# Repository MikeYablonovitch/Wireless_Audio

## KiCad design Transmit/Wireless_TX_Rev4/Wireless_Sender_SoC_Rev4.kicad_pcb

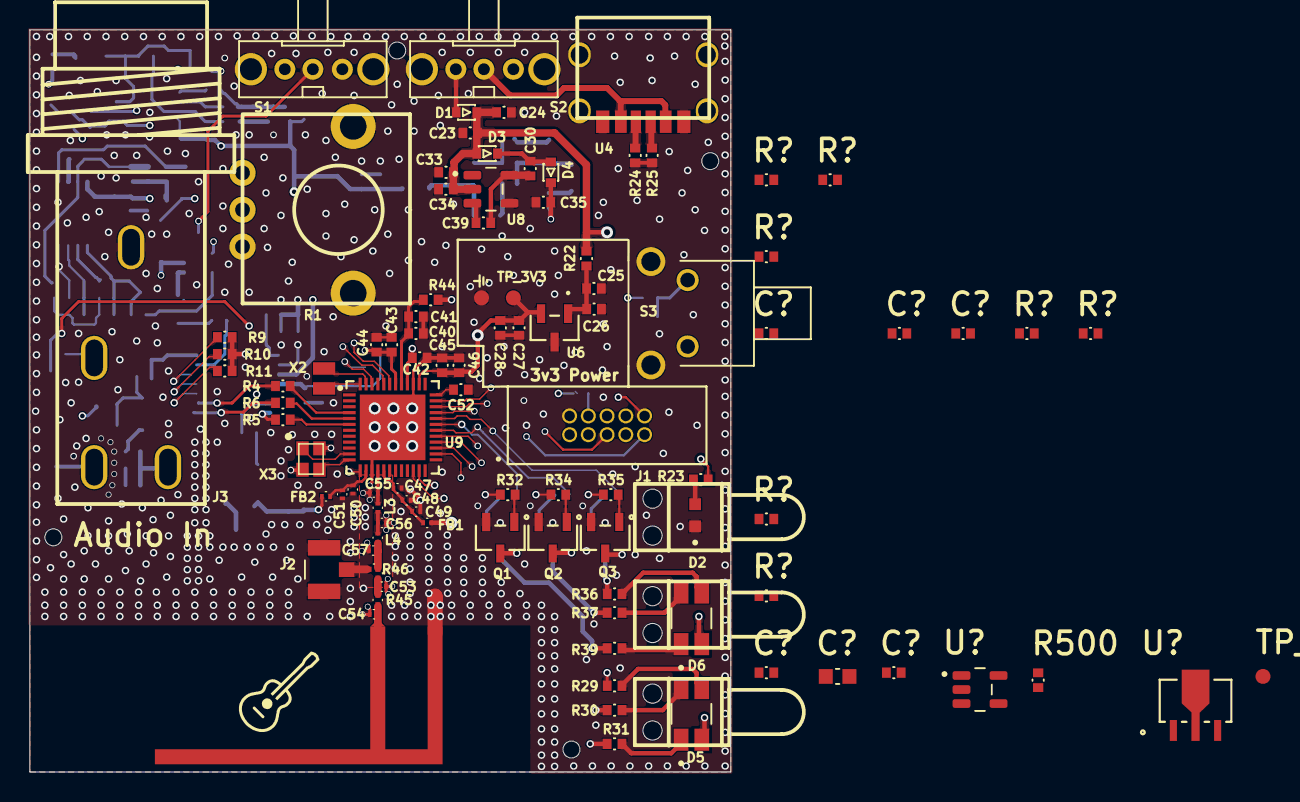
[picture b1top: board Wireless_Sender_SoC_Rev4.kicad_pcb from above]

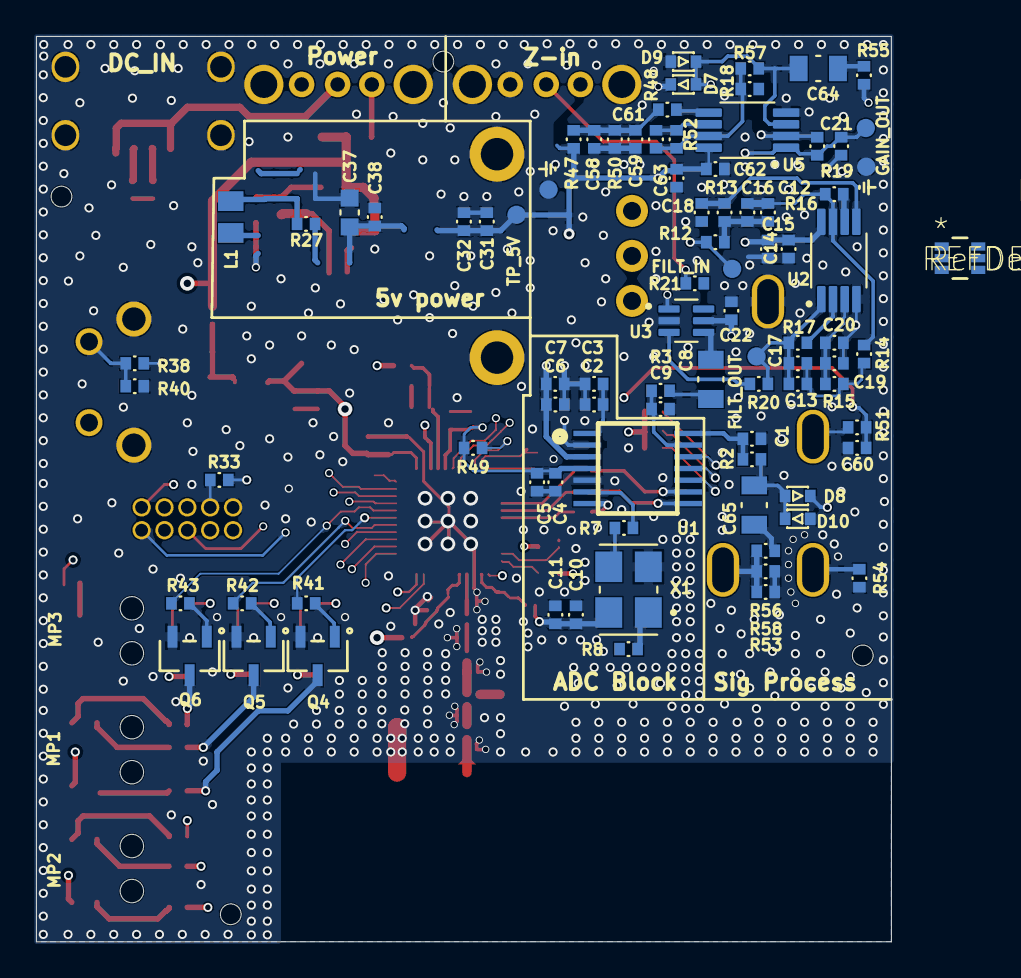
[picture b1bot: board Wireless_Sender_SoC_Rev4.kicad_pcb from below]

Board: 4 copper layers, 47.5 x 50.3 mm, 187 parts (87 on the bottom side), 112 nets.

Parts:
AT1: INVERTED_F
C1: DNP; Capacitor_0402
C2, C5, C6, C10, C24, C26, C41, C42, C44, C45: 100n; CAPACITOR_0402
C3, C4, C7, C11: 2u2; CAPACITOR_0402
C8, C64, C65: 100n; CAPACITOR_0805
C9, C21, C61: DNP; CAPACITOR_0402
C12, C13, C18: 2n7; CAPACITOR_0402
C14, C27, C31, C38, C40, C43, C52, C59, C62: 1u; CAPACITOR_0402
C15, C28, C32, C46, C63: 10u; CAPACITOR_0402
C16, C19: 390p; CAPACITOR_0402
C17: 4n7; CAPACITOR_0402
C20: 680p; CAPACITOR_0402
C22, C23: 1u; Capacitor_0402
C25, C30, C33, C35, C39: 2u2; Capacitor_0402
C34: 100n; Capacitor_0402
C37: 10u; CAPACITOR_0603
C47: 0p5; CAPACITOR_0201
C48, C50: 18p; CAPACITOR_0201
C49: 1u; CAPACITOR_0201
C51: 2u2; CAPACITOR_0201
C53, C54: DNP; CAPACITOR_0201
C55: 2p3; CAPACITOR_0201
C56: 1p6; CAPACITOR_0201
C57: 0p3; CAPACITOR_0201
C58: 10n; CAPACITOR_0402
C60: 1nF; CAPACITOR_0402
C?: 1u; Capacitor_0402
C?#2: 10n; Capacitor_0402
C?#3: 10u; Capacitor_0402
C?#4: 10u; Capacitor_0603
C?#5, C?#6: 1u; Capacitor_0402
D1, D3, D4: 300mV; SOD523
D2: 0603 LED; LED_SM0603UYC
D5, D6: LED RGB DIFFUSED CHIP SMD; LED_HSMF-C118
D7, D8, D9, D10: 370mV; SOD523
FB1, FB2: BLM03AG700SN1D; FERRITE_BEAD_0201
J1: CONN HEADER VERT 10POS 1.27MM; CONN_3220-10-0100-00_CNC
J2: U.FL-R-SMT; HIROSE_U.FL-R-SMT-1(80)
J3: -20℃~+70℃ 6.35mm Headphone Jack 30V 500mA Plugin 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; AUDIO-TH_PJ-603
L1: 3.3uH; INDUCTOR 0805
L3: 2n9; INDUCTOR_0201
L4: 1n2; INDUCTOR_0201
MP1, MP2, MP3: SLP3-200-200-R
Q1, Q2, Q3, Q4, Q5, Q6: MOSFET N-CH 60V 115MA SOT23; SOT-23_MCC
R1: 10K_Pot; RK09L1140
R2, R3, R18, R32, R34, R35, R38, R41, R42, R43, R52, R55, R56: 1k; RESISTOR_0402
R4, R5, R6, R7, R19, R20, R33: 49r9; RESISTOR_0402
R8, R9, R10, R11, R23, R40, R47, R48, R50: 10k; RESISTOR_0402
R12, R13, R14, R15, R16, R17, R29, R30, R31, R36, R37, R39: 5.6k; RESISTOR_0402
R21, R24, R25: 10k; Resistor_0402
R22: 0r; RESISTOR_0402
R27, R44: 2r; RESISTOR_0402
R45: 0r; RESISTOR_0201
R46: 0r; RESISTOR_0201 - 2-WAY
R49, R53, R54: 10M; RESISTOR_0402
R51: 100k; RESISTOR_0402
R57: 1M; RESISTOR_0402
R58: 24k9; RESISTOR_0402
R500: DNP; Resistor_0402
R?: DNP; Resistor_0402
R?#2, R?#4, R?#6, R?#7: DNP; Resistor_0402
R?#3, R?#5: 1k; Resistor_0402
S1, S2: Slide Switch; OS102011MA1Q
S3: Switch Push Button; SW_1-1825027-1
TP_3V3, TP_5V: Test Point; TEST_POINT_ROUND_40
TP_CP: Test Point; TEST_POINT_ROUND_40
TP_FILT_IN: Test Point; TEST_POINT_ROUND_40
TP_FILT_OUT: Test Point; TEST_POINT_ROUND_40
TP_GAIN_OUT: Test Point; TEST_POINT_ROUND_40
TP_GND1, TP_GND2, TP_GND3: Test Point; TEST_POINT_ROUND_40_GND
U1: 24 serial TSSOP-14 ADCs/DACs - Special Purpose RO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; TSSOP-14
U2, U5: OPA2376AIDGKR; SOP65P490X110-8N
U3: IC SWITCH SPDT X 1 15OHM SC70-6; SOT65P210X110-6N
U4: TYPE-C 6P(073)
U6: IC REG LIN 3.3V 300MA SOT23-3; AP7375-33SA-7_DIO
U8: UNREGULATED 60-mA CHARGE PUMP VOLTAGE INVERTER; SOT95P280X145-5N
U9: EFR32MG24B220F1536IM48-B; QFN48_0p4_6sq_SIL
U?: IC REG LINEAR 5.5V 150MA SOT-89-3; SOT-89_3MC_MCH
U?#2: TPS7A2050 - 5V 300MA SOT23-5; SOT95P280X145-5N
U?#3: MCP4017T-103E/LTY; SOP_MCP4017T-103ELTY_MCH
X1: 12.288MHz 3.3V ±10ppm CMOS; XTAL_ASFL1-12.288MHZ-EC-T
X2: 32.768kHz; DST210AC
X3: 39MHz 10pF ±8ppm; TZ3541C

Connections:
3V_DIGITAL: C4.1, C5.1, C10.1, C11.1, C27.1, C28.1, C42.1, C43.1, C44.1, C45.1, C46.1, FB1.2, FB2.2, J1.1, R1.1, R8.2, R9.2, R10.2, R11.2, R44.2, R49.2, S3.1, TP_3V3.1, U1.4, U6.2, U9.38, U9.40, U9.42, X1.4
5V_ANALOG: C6.1, C7.1, C14.1, C15.1, C22.1, C31.1, C32.1, C62.1, C63.1, C?.1, C?#3.1, D7.Cathode, D8.Cathode, R21.1, R47.2, TP_5V.1, U1.3, U2.8, U3.5, U5.8, U?#2.5, U?#3.1
ADC_I2S_BCLK: R6.1, U9.5
ADC_I2S_DATA: R4.1, U9.4
ADC_I2S_LRCLK: R5.2, U9.6
ANTI_ALIAS_IN: R12.2, R19.1, R?#4.1, TP_FILT_IN.1
ANTI_ALIAS_OUT: C13.2, C17.2, R17.1, R20.1, TP_FILT_OUT.1, U2.1
ANT_OUT: C53.1, R45.1, R46.2
ANT_OUT_MATCHED: AT1.1, C54.1, R45.2
AUDIO_HOT_PLUG_DETECT: C60.2, R49.1, R51.1, U9.46
BUTTON_IN: R38.1, U9.35
FMT: R9.1, U1.12
GAIN_OUT: C21.1, R19.2, R?#5.2, TP_GAIN_OUT.1, U5.1
GND: AT1.2, C1.2, C2.2, C3.2, C4.2, C5.2, C6.2, C7.2, C9.2, C10.2, C11.2, C14.2, C15.2, C18.2, C19.2, C20.2, C22.2, C23.1, C24.1, C25.2, C26.2, C27.2, C28.2, C31.2, C32.2, C33.2, C34.2, C35.2, C37.2, C38.2, C40.2, C41.2, C42.2, C43.2, C44.2, C45.2, C46.2, C47.2, C48.2, C49.2, C50.2, C51.2, C52.2, C53.2, C54.2, C55.2, C56.2, C57.2, C58.2, C59.2, C60.1, C62.2, C63.2, C?#2.2, C?#4.2, C?#5.2, C?#6.2, D2.C, D9.Anode, D10.Anode, J1.2, J2.G1, J2.G2, J3.2, Q1.2, Q2.2, Q3.2, Q4.2, Q5.2, Q6.2, R1.3, R1.4, R1.5, R24.2, R25.2, R40.2, R50.2, R53.1, R54.1, R58.1, R500.2, R?.1, R?#2.2, R?#4.2, R?#6.2, R?#7.1, S1.1, S1.MT1, S1.MT2, S2.MT1, S2.MT2, S3.S1, S3.S2, TP_GND1.1, TP_GND2.1, TP_GND3.1, U1.2, U1.5, U2.4, U3.2, U4.A12, U4.B12, U4.SHIELD, U5.4, U6.3, U8.4, U9.15, U9.39, U9.49, U?#2.2, X1.2, X3.2, X3.4
HFXTAL_I: U9.11, X3.1
HFXTAL_O: U9.12, X3.3
LFXO_I: U9.47, X2.1
LFXO_O: U9.48, X2.2
MD0: R11.1, U1.10
MD1: R10.1, U1.11
NetC1_1: C1.1, R2.1, U1.14
NetC2_1: C2.1, C3.1, U1.1
NetC8_1: C8.1, R3.2
NetC9_1: C9.1, R3.1, U1.13
NetC12_1: C12.1, C16.1, R12.1, R13.2
NetC12_2: C12.2, C16.2, R14.2, R16.1, U2.7
NetC13_1: C13.1, C17.1, R14.1, R15.2
NetC18_1: C18.1, R13.1, U2.5
NetC19_1: C19.1, C20.1, R15.1, U2.3
NetC21_2: C21.2, R?#3.2, U5.2
NetC25_1: C25.1, C26.1, R22.1, U6.1
NetC30_1: C30.1, D3.Cathode, D4.Anode
NetC30_2: C30.2, C39.1, U8.5
NetC35_1: C35.1, D4.Cathode, L1.2, TP_CP.1
NetC37_1: C37.1, C38.1, C?#6.1, U?.3, U?#2.1, U?#2.3
NetC39_2: C39.2, U8.3
NetC40_1: C40.1, C41.1, R44.1, U9.41
NetC47_1: C47.1, C48.1, C49.1, FB1.1, U9.17
NetC50_1: C50.1, C51.1, FB2.1, U9.14
NetC52_1: C52.1, U9.36
NetC56_1: C56.1, L3.2, L4.1
NetC58_1: C58.1, C59.1, R47.1, R48.1, R50.1
NetC61_2: C61.2, R52.2, U5.6
NetC64_2: C64.2, R55.1
NetC65_2: C65.2, R56.1
NetC?_1: C?#4.1, C?#5.1, R27.1, U?.2
NetC?_2: C?.2, C?#3.2, U?#3.2
NetD1_Anode: D1.Anode, S2.3
NetD2_A: D2.A, R23.2
NetD5_2: D5.2, R29.2
NetD5_3: D5.3, R30.2
NetD5_4: D5.4, R31.2
NetD6_2: D6.2, R36.2
NetD6_3: D6.3, R37.2
NetD6_4: D6.4, R39.2
NetJ1_4: J1.4, R33.2
NetJ3_3: J3.3, R51.2
NetL1_1: L1.1, R27.2
NetQ1_1: Q1.1, R32.1
NetQ1_3: Q1.3, R31.1
NetQ2_1: Q2.1, R34.2
NetQ2_3: Q2.3, R30.1
NetQ3_1: Q3.1, R35.1
NetQ3_3: Q3.3, R29.1
NetQ4_1: Q4.1, R41.1
NetQ4_3: Q4.3, R39.1
NetQ5_1: Q5.1, R42.2
NetQ5_3: Q5.3, R37.1
NetQ6_1: Q6.1, R43.2
NetQ6_3: Q6.3, R36.1
NetR4_2: R4.2, U1.9
NetR5_1: R5.1, U1.7
NetR6_2: R6.2, U1.8
NetR7_2: R7.2, X1.3
NetR8_1: R8.1, X1.1
NetR16_2: R16.2, U2.6
NetR17_2: R17.2, U2.2
NetR18_2: R18.2, R?#3.1, U?#3.5
NetR20_2: R20.2, R?#2.1, U3.3
NetR21_2: R21.2, S1.2, U3.6
NetR24_1: R24.1, U4.B5
NetR25_1: R25.1, U4.A5
NetR38_2: R38.2, R40.1, S3.2
NetR48_2: R48.2, U5.5
NetR?_1: R?#5.1, U?#3.6
NetS2_2: S2.2, U4.A9, U4.B9
OP_AMP_BIAS: C61.1, R18.1, R52.1, R57.1, R?#6.1, U5.7
PTI_DATA: J1.10, U9.44
PTI_FRAME: J1.9, U9.43
Pot_Output: C?#2.1, R1.2
RESET: J1.3, U9.13
RF_OUT: C55.1, L3.1, U9.16
RF_OUT_MATCHED: C57.1, L4.2, R46.1
RGB_1_B_PWM: R32.2, U9.22
RGB_1_G_PWM: R34.1, U9.23
RGB_1_R_PWM: R35.2, U9.26
RGB_2_B_PWM: R41.2, U9.31
RGB_2_G_PWM: R42.1, U9.30
RGB_2_R_PWM: R43.1, U9.32
SCK_FROM_TCXO: R7.1, U1.6
SLEEVE_BIAS_OUT: C65.1, D8.Anode, D10.Cathode, R2.2, R?#7.2
SLEEVE_SIGNAL_IN: J3.5, R53.2, R56.2, R58.2
SWCLK: J1.8, U9.27
SWDIO: J1.7, U9.28
SWO: J1.6, U9.29
TIP_ADC_IN: C8.2, R?.2, U3.4
TIP_SIGNAL_IN: J3.4, R54.2, R55.2
TIP_SIGNAL_IN_BIASED: C64.1, D7.Anode, D9.Cathode, R57.2, U3.1, U5.3
UFL_OUT: J2.SIG, R46.3
VCOM_RX: R33.1, U9.34
VCOM_TX: J1.5, U9.33
VIN: C23.2, C24.2, C33.1, C34.1, D1.Cathode, D3.Anode, D5.1, D6.1, R22.2, R23.1, U8.2

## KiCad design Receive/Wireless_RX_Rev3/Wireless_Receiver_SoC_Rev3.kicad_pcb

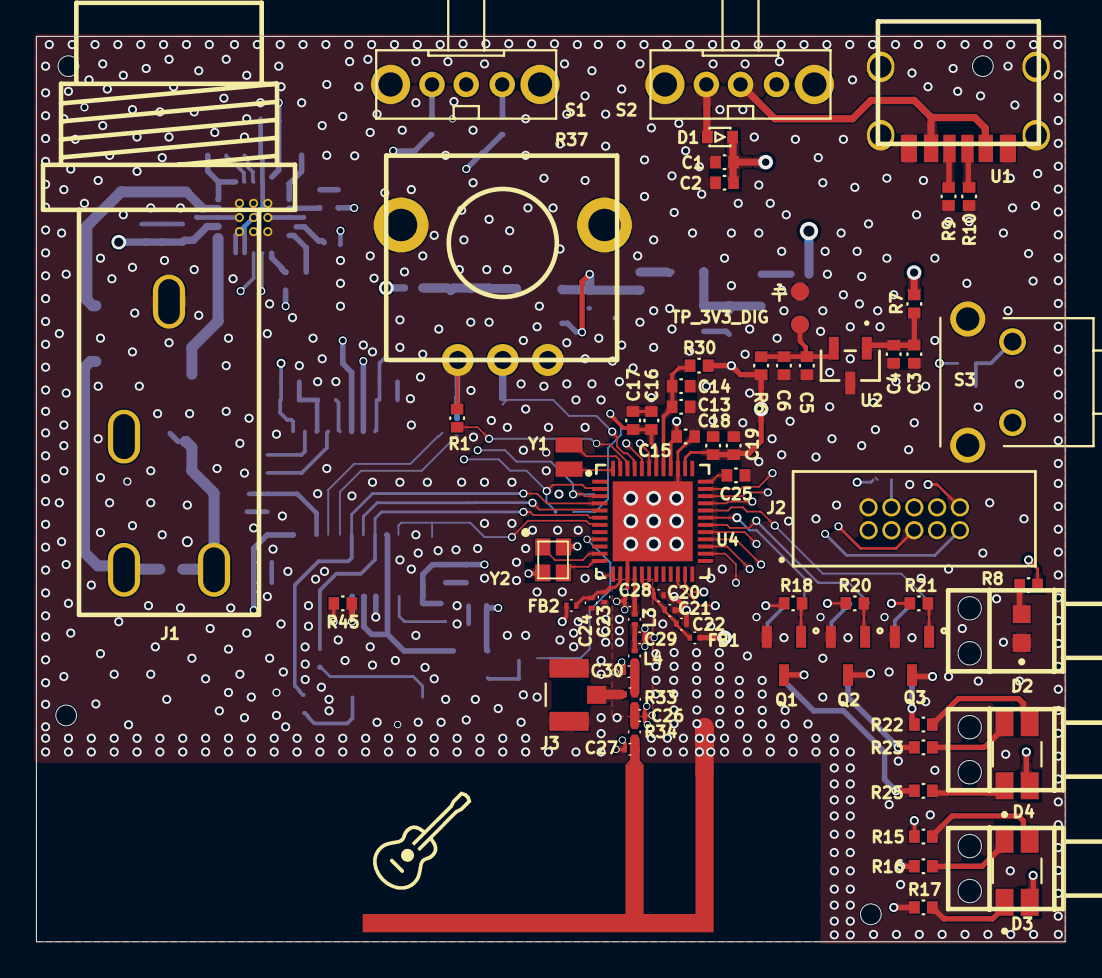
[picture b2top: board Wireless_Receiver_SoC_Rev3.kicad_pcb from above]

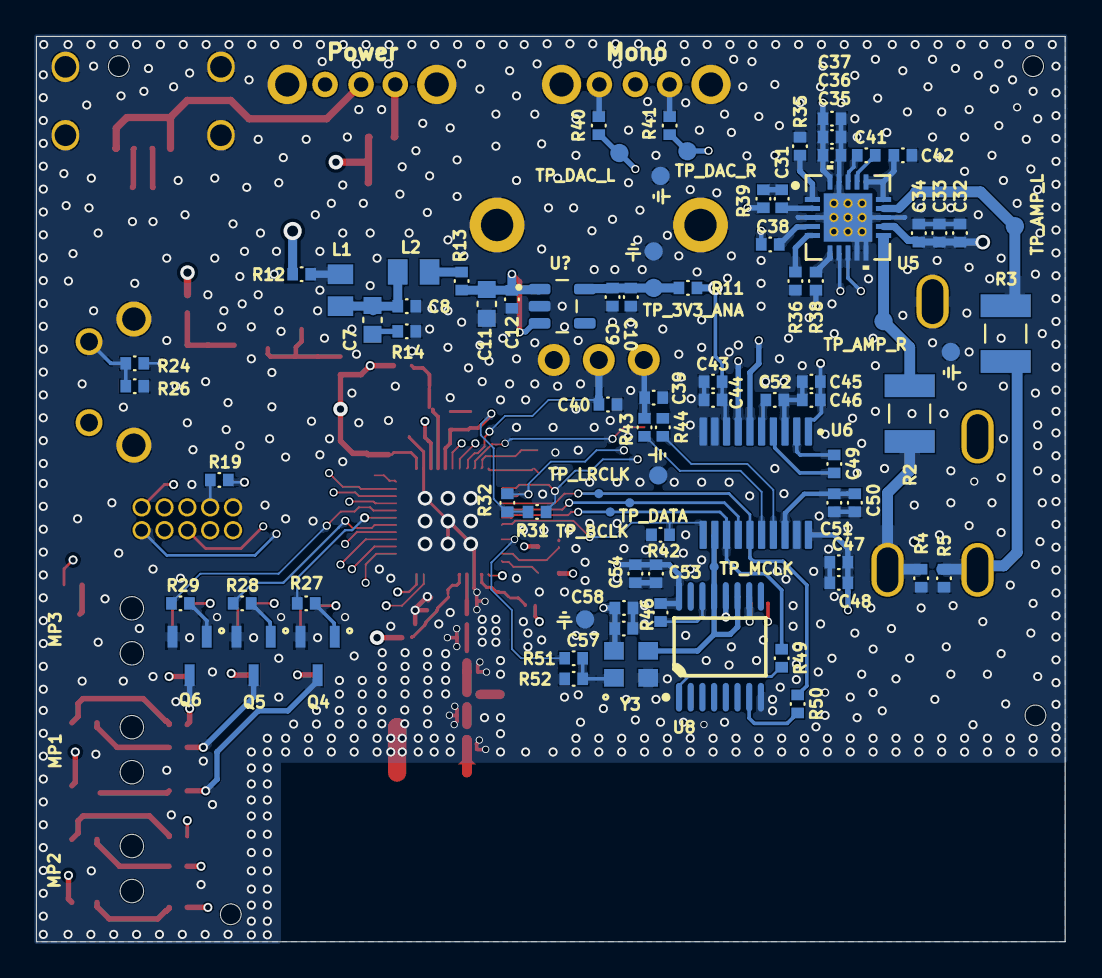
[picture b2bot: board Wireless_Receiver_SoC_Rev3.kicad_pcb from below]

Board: 4 copper layers, 57.1 x 50.3 mm, 158 parts (86 on the bottom side), 105 nets.

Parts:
AT1: INVERTED_F
C1, C9, C33, C36, C39, C41, C42, C44, C45, C48, C51, C54, C58: 1u; Capacitor_0402
C2, C34, C35, C46, C47, C53, C57: 100n; Capacitor_0402
C3: 2u2; Capacitor_0402
C4, C5, C8, C12, C13, C16, C25: 1u; CAPACITOR_0402
C6, C19: 10u; CAPACITOR_0402
C7, C11: 10u; CAPACITOR_0603
C10, C32, C37, C43, C50: 10u; Capacitor_0402
C14, C15, C17, C18: 100n; CAPACITOR_0402
C20: 0.5p; CAPACITOR_0201
C21, C23: 18p; CAPACITOR_0201
C22: 1u; CAPACITOR_0201
C24: 2.2u; CAPACITOR_0201
C26, C27: DNP; CAPACITOR_0201
C28: 2.3p; CAPACITOR_0201
C29: 1.6p; CAPACITOR_0201
C30: 0.3p; CAPACITOR_0201
C31, C38: 470n; Capacitor_0402
C40: 10n; Capacitor_0402
C49, C52: 2.2uF; Capacitor_0402
D1: 300mV; SOD523
D2: 0603 LED; LED_SM0603UYC
D3, D4: 1210 Red, Green, Blue (RGB); LED_HSMF-C118
FB1, FB2: BLM03AG700SN1D; FERRITE_BEAD_0201
J1: -20℃~+70℃ 6.35mm Headphone Jack 30V 500mA Plugin 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; AUDIO-TH_PJ-603
J2: CONN HEADER VERT 10POS 1.27MM; CONN_3220-10-0100-00_CNC
J3: U.FL-R-SMT; HIROSE_U.FL-R-SMT-1(80)
L1, L2: 3.3uH; INDUCTOR 0805
L3: 2.9n; INDUCTOR_0201
L4: 1.2n; INDUCTOR_0201
MP1, MP2, MP3: SLP3-200-200-R
Q1, Q2, Q3, Q4, Q5, Q6: MOSFET N-CH 60V 115MA SOT23; SOT-23_MCC
R1, R4, R5, R26: 10k; RESISTOR_0402
R2, R3: 39r; Resistor_1210
R6, R11, R35, R36: 0r; Resistor_0402
R7, R12: 0r; RESISTOR_0402
R8, R38, R42, R43, R44, R45, R46: 10k; Resistor_0402
R9, R10: 5k1; Resistor_0402
R13, R14, R30: 2r; RESISTOR_0402
R15, R16, R17, R22, R23, R25: 5.6k; RESISTOR_0402
R18, R20, R21, R24, R27, R28, R29: 1k; RESISTOR_0402
R19: 49r9; RESISTOR_0402
R31, R32: DNP; Resistor_0402
R33: Resistor_2-way-no-stub; RESISTOR_0201 - 2-WAY
R34: 0r; RESISTOR_0201
R37: 10K_Pot; RK09L1140
R39, R40, R41, R51: 1k; Resistor_0402
R49, R50: 49r9; Resistor_0402
R52: NC; Resistor_0402
S1, S2: Slide Switch; OS102011MA1Q
S3: Switch Push Button; SW_1-1825027-1
TP_3V3_ANA, TP_3V3_DIG: Test Point; TEST_POINT_ROUND_40
TP_AMP_L: Test Point; TEST_POINT_ROUND_40
TP_AMP_R: Test Point; TEST_POINT_ROUND_40
TP_BCLK: Test Point; TEST_POINT_ROUND_20
TP_DAC_L: Test Point; TEST_POINT_ROUND_40
TP_DAC_R: Test Point; TEST_POINT_ROUND_40
TP_DATA: Test Point; TEST_POINT_ROUND_20
TP_GND1, TP_GND2: Test Point; TEST_POINT_ROUND_40_GND
TP_GND?: Test Point; TEST_POINT_ROUND_40_GND
TP_GND?#2, TP_GND?#3, TP_GND?#4: Test Point; TEST_POINT_ROUND_40_GND
TP_LRCLK: Test Point; TEST_POINT_ROUND_20
TP_MCLK: Test Point; TEST_POINT_ROUND_20
U1: TYPE-C 6P(073)
U2: IC REG LIN 3.3V 300MA SOT23-3; AP7375-33SA-7_DIO
U4: EFR32MG24B220F1536IM48-B; QFN48_0P4_6SQ_SIL
U5: Class AB QFN-20-EP(4x4) Audio Amplifiers; RTJ20_2P7X2P7
U6: PCM5100PWR; SOP65P640X120-20N
U8: IC BINARY COUNTER 8-BIT 16TSSOP; TI TSSOP-16 PW
U?: TPS7A2033PDBVR; SOT95P280X145-5N
Y1: SMD2012-2P Crystals ROHS; DST210AC
Y2: 39MHz 10pF ±8ppm SMD2016-4P Crystals ROHS; TZ3541C
Y3: 12.288MHz VCXO; SMD4_SIT3808AC_3p2x2p5x0p75_SIT

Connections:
3v_analog: C32.2, C33.1, C34.1, C35.1, C36.1, C37.2, C43.2, C44.2, C45.2, C46.2, R11.1, R38.2, U5.12, U5.20, U6.1, U6.8
3v_digital: C15.1, C16.1, C17.1, C18.1, C19.1, C39.1, C47.2, C48.2, C53.1, C54.1, C57.1, C58.1, FB1.2, FB2.2, J2.1, R1.2, R6.1, R30.2, R31.1, R32.1, R37.1, R43.2, R45.1, R46.1, S3.1, U4.38, U4.40, U4.42, U6.20, U8.16, Y3.4
-3v3: C52.2, U6.5
AMP_OUT_L: R3.2, TP_AMP_L.1, U5.14
AMP_OUT_R: R2.2, TP_AMP_R.1, U5.11
ANT_OUT: C26.1, R33.2, R34.1
ANT_OUT_MATCHED: AT1.1, C27.1, R34.2
AUDIO_HOT_PLUG_DETECT: J1.3, R1.1, U4.46
BUTTON_IN: R24.1, U4.35
DAC_BCLK: R49.2, TP_BCLK.1, U4.6, U6.13
DAC_DATA: TP_DATA.1, U4.5, U6.14
DAC_LRCLK: R50.2, TP_LRCLK.1, U4.4, U6.15
DAC_MCLK: TP_MCLK.1, U6.12, U8.11, U8.13, Y3.3
FLT: R42.1, U4.7, U6.11
GND: AT1.2, C1.1, C2.1, C3.2, C4.2, C5.2, C6.2, C8.2, C9.2, C10.2, C11.2, C12.2, C13.2, C14.2, C15.2, C16.2, C17.2, C18.2, C19.2, C20.2, C21.2, C22.2, C23.2, C24.2, C25.2, C26.2, C27.2, C28.2, C29.2, C30.2, C32.1, C33.2, C34.2, C35.2, C36.2, C37.1, C39.2, C40.2, C42.1, C43.1, C44.1, C45.1, C46.1, C47.1, C48.1, C50.1, C51.1, C52.1, C53.2, C54.2, C57.2, C58.2, D2.C, J1.2, J2.2, J3.G1, J3.G2, Q1.2, Q2.2, Q3.2, Q4.2, Q5.2, Q6.2, R4.1, R5.1, R9.2, R10.2, R14.2, R26.2, R35.2, R36.2, R37.3, R37.4, R37.5, R42.2, R44.2, R52.2, S1.MT1, S1.MT2, S2.MT1, S2.MT2, S3.S1, S3.S2, TP_GND1.1, TP_GND2.1, TP_GND?.1, TP_GND?#2.1, TP_GND?#3.1, TP_GND?#4.1, U1.A12, U1.B12, U1.SHIELD, U2.3, U4.15, U4.39, U4.49, U5.3, U5.9, U5.10, U5.13, U5.19, U5.21, U6.3, U6.9, U6.10, U6.19, U8.8, U8.12, U?.2, Y2.2, Y2.4, Y3.2
HFXTAL_I: U4.11, Y2.1
HFXTAL_O: U4.12, Y2.3
LFXO_I: U4.47, Y1.1
LFXO_O: U4.48, Y1.2
MUTE: R44.1, U6.17
NetC3_1: C3.1, C4.1, R7.1, U2.1
NetC5_1: C5.1, C6.1, R6.2, TP_3V3_DIG.1, U2.2
NetC7_1: C7.1, C8.1, L1.1, L2.2
NetC7_2: C7.2, R14.1
NetC9_1: C9.1, C10.1, R11.2, TP_3V3_ANA.1, U?.5
NetC11_1: C11.1, C12.1, R13.1, U?.1, U?.3
NetC13_1: C13.1, C14.1, R30.1, U4.41
NetC20_1: C20.1, C21.1, C22.1, FB1.1, U4.17
NetC23_1: C23.1, C24.1, FB2.1, U4.14
NetC25_1: C25.1, U4.36
NetC29_1: C29.1, L3.2, L4.1
NetC31_1: C31.1, U5.2
NetC38_1: C38.1, U5.4
NetC41_1: C41.1, U5.18
NetC41_2: C41.2, U5.17
NetC42_2: C42.2, U5.15, U5.16
NetC49_1: C49.1, U6.2
NetC49_2: C49.2, U6.4
NetC50_2: C50.2, C51.2, U6.18
NetD1_Anode: D1.Anode, S2.3
NetD2_A: D2.A, R8.2
NetD3_2: D3.2, R15.2
NetD3_3: D3.3, R16.2
NetD3_4: D3.4, R17.2
NetD4_2: D4.2, R22.2
NetD4_3: D4.3, R23.2
NetD4_4: D4.4, R25.2
NetJ1_4: J1.4, R3.1, R5.2
NetJ1_5: J1.5, R2.1, R4.2
NetJ2_4: J2.4, R19.2
NetL1_2: L1.2, R12.1
NetL2_1: L2.1, R13.2
NetQ1_1: Q1.1, R18.1
NetQ1_3: Q1.3, R17.1
NetQ2_1: Q2.1, R20.2
NetQ2_3: Q2.3, R16.1
NetQ3_1: Q3.1, R21.1
NetQ3_3: Q3.3, R15.1
NetQ4_1: Q4.1, R27.1
NetQ4_3: Q4.3, R25.1
NetQ5_1: Q5.1, R28.2
NetQ5_3: Q5.3, R23.1
NetQ6_1: Q6.1, R29.2
NetQ6_3: Q6.3, R22.1
NetR9_1: R9.1, U1.B5
NetR10_1: R10.1, U1.A5
NetR24_2: R24.2, R26.1, S3.2
NetR35_1: R35.1, U5.1
NetR36_1: R36.1, U5.5
NetR38_1: R38.1, U5.6
NetR39_1: R39.1, R40.1, TP_DAC_L.1, U6.6
NetR40_2: R40.2, S1.1
NetR41_1: R41.1, TP_DAC_R.1, U6.7
NetR41_2: R41.2, S1.3
NetR43_1: R43.1, U6.16
NetR45_2: R45.2, U8.10
NetR46_2: R46.2, U8.14
NetR49_1: R49.1, U8.1
NetR50_1: R50.1, U8.7
NetR51_2: R51.2, R52.1, Y3.1
NetS2_2: S2.2, U1.A9, U1.B9
POT_OUT_L: C31.2, R39.2
POT_OUT_R: C38.2, S1.2
PTI_DATA: J2.10, U4.44
PTI_FRAME: J2.9, U4.43
RESET: J2.3, U4.13
RF_OUT: C28.1, L3.1, U4.16
RF_OUT_MATCHED: C30.1, L4.2, R33.1
RGB_1_B_PWM: R18.2, U4.22
RGB_1_G_PWM: R20.1, U4.23
RGB_1_R_PWM: R21.2, U4.26
RGB_2_B_PWM: R27.2, U4.31
RGB_2_G_PWM: R28.1, U4.30
RGB_2_R_PWM: R29.1, U4.32
SCL: R32.2, U4.3, U5.8
SDA: R31.2, U4.2, U5.7
SWCLK: J2.8, U4.27
SWDIO: J2.7, U4.28
SWO: J2.6, U4.29
UFL_OUT: J3.SIG, R33.3
VCOM_RX: R19.1, U4.34
VCOM_TX: J2.5, U4.33
VCXO_CONTROL: R51.1, U4.9
VIN: C1.2, C2.2, D1.Cathode, D3.1, D4.1, R7.2, R8.1, R12.2
VOLUME_CONTROL: C40.1, R37.2, U4.45
